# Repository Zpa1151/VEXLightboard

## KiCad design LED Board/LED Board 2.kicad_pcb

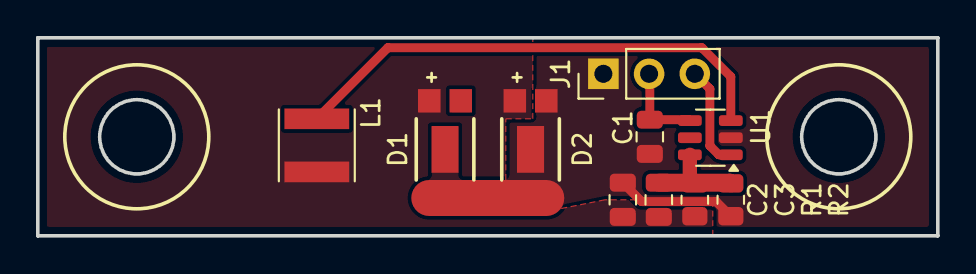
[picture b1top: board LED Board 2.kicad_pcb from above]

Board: 2 copper layers, 50.0 x 11.0 mm, 10 parts (0 on the bottom side), 6 nets.

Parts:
C1: 4.7uF; C_0805_2012Metric
C2: 10uF; C_0805_2012Metric
C3: 6.8pF; C_0805_2012Metric
D1, D2: WL-SWTP_5630
J1: Connector; PinHeader_1x03_P2.54mm_Vertical
L1: 2.2uH; L_Vishay_IFSC-1515AH_4x4x1.8mm
R1: 200k; R_0805_2012Metric
R2: 50k; R_0805_2012Metric
U1: TLV62569DDC; SOT-23-6

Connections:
+3V: C2.2, C3.1, D1.3, D2.3, L1.2, R1.1
+5V: C1.2, J1.2, U1.4 (VIN)
+5VD: J1.3, U1.1 (EN)
Earth: C1.1, C2.1, D1.1, D1.2, D1.4, D1.5, D2.1, D2.2, D2.4, D2.5, J1.1, R2.2, U1.2 (GND)
unnamed: C3.2, R1.2, R2.1, U1.6 (FB)
unnamed: L1.1, U1.3 (SW)

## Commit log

2025-10-28 Replaced LED and redid the layout
